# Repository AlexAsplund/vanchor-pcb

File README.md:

# Vanchor PCBs (helm v4.2 + thrust driver v1.1)

Carrier PCB for the [vanchor-ng](../vanchor-ng) trolling-motor autopilot:
an **Orange Pi Zero 3** (autopilot computer) + **Raspberry Pi Pico 2**
(real-time motor controller, I²C slave) on one **125×95 mm 2-layer board
(standard 1 oz)**. Thrust power lives on the companion **thrust-driver
board** cabled to J13 (any IBT-2/BTS7960-class driver also works); the
steering-servo bridge is on board. **12 V-only** (car battery, 14.4 V
charging) — the 5 V rail comes from an XL4015 buck module soldered on as a
daughterboard (U5). Full system diagrams: **`docs/architecture.md`**.

```mermaid
graph LR
    BATT[("12V battery")] -->|"J16, F1 10A, rev-FET"| VIN["VIN"]
    BATT ==>|"fat cable + ANL fuse"| TD["thrust driver board<br/>(J13 8-wire cable)"]
    VIN --> U5["U5 XL4015 buck 5V"] --> SBC["Orange Pi Zero 3 / RPi<br/>(J1 ribbon) + screen + fan"]
    VIN --> SRV["2x BTN8982TA servo bridge"] -->|"J22"| SM["12V worm servo"]
    SBC <-->|"I2C3"| PICO["Pico 2 @0x42"]
    PICO -->|"GP12-15 PWM"| TD --> M(("trolling motor"))
    PICO --> SRV
    SM -->|"AS5600, J11"| PICO
    SBC -.->|"WiFi"| TAB["tablet"]
    HWT["HWT901B AHRS"] -->|"J3 UART5"| SBC
    PICO <-->|"can2040 + J12 xcvr + J5"| N2K[("NMEA2000")]
```

*[static SVG](docs/diagrams/readme-overview.svg) — full diagram set: `docs/architecture.md`*

Cost history: v1/v2 carried an on-board 800 W H-bridge; ten documented
cost-optimization passes (see `docs/cost-optimization-log.md`) brought a
12 V build from ~$111 to **~$41 per assembled board** (~$35 parts + ~$6 PCB).
The v2 on-board-bridge design remains available at git tag/commit `bf91c4a`.

## NMEA2000 / CAN provision (helm board)

CAN lives on the Pico 2 (can2040 PIO CAN on GP18/GP19, 250 kbit/s for
NMEA2000). Plug a 3.3 V CAN transceiver module (Waveshare SN65HVD230) onto
J12 with four jumper wires: pin 1 = 3V3, pin 8 = GND, pin 6 = GP18 -> CTX,
pin 7 = GP19 -> CRX. The N2K drop cable's CAN_H/L land on the module's
screw terminal; its power/shield conductors land on J5 (V+ / GND / SHIELD).
R41 (0R, DNP): fit to power the backbone from the battery input - add an
inline 2-3 A fuse in the drop cable if you do. R42 (0R, DNP): bond shield
to GND only if the network isn't grounded elsewhere.

## Boards

- `boards/helm/` — the helm/carrier board (Orange Pi Zero 3 *or* Raspberry Pi + Pico 2, servo
  bridge, XL4015 buck daughterboard, PWM output header J13).
- `boards/thrust-driver/` — 12-24 V trolling-motor H-bridge (2-4× BTN8982TA),
  connects to helm J13 with a straight 8-wire cable. See its README for the
  base (~30 A) vs high-power (~50 A) variants and the solder-lane
  reinforcement technique.

## Repository layout

| Path | Content |
|---|---|
| `boards/helm/` | KiCad 10 project (schematic, board, custom symbols/footprints) |
| `boards/helm/sheets/*.py` | Net-spec sources — the schematic is **generated** from these |
| `boards/helm/scripts/` | Generators + gates (`build_sch.sh`, `build_board.py`, ERC/DRC helpers) |
| `boards/helm/fab/` | Gerbers, drill, BOM — upload these to PCBWay/JLCPCB |
| `boards/thrust-driver/` | Companion H-bridge board (own README, sheets, scripts, fab) |
| `docs/architecture.md` | **System diagrams**: WiFi/tablet, NMEA0183+2000, HWT901B, control loop |
| `docs/cost-optimization-log.md` | The 10 cost passes and their effect |
| `docs/superpowers/` | Design spec + implementation plan |
| `.claude/skills/` | kicad-happy review skills (vendored) |

## Regenerating the design

```sh
docker compose up -d                 # KiCad 10 container (GUI at https://localhost:3001)
./boards/helm/scripts/build_sch.sh      # specs -> .kicad_sch + ERC
docker exec vanchor-kicad kicad-cli sch export netlist --format kicadsexpr \
    -o /config/vanchor-pcb/boards/helm/vanchor-helm.net /config/vanchor-pcb/boards/helm/vanchor-helm.kicad_sch
docker exec -e BASE_GND=0 vanchor-kicad python3 /config/vanchor-pcb/boards/helm/scripts/build_board.py
# route with freerouting-1.9 (see git history for the exact docker command),
# then: docker exec vanchor-kicad python3 /config/vanchor-pcb/boards/helm/scripts/import_routes.py
```

## Connector map

| Ref | Label | Wire to |
|---|---|---|
| J16 | BATT 12V | battery + / − (board logic + servo supply; ≥1.5 mm²) |
| J13 | THRUST DRV | external driver, IBT-2 pin order: **1 RPWM · 2 LPWM · 3 R_EN · 4 L_EN · 5 R_IS · 6 L_IS · 7 VCC(5V) · 8 GND** |
| J22 | SERVO MOTOR | 12 V worm gearmotor of the steering servo |
| U5 | XL4015 BUCK | the module solders ON: pins into its 4 corner terminals, spacers, into the slotted pads (set 5.1 V first!) |
| J1 | OPI Z3 26-PIN | male header → 26-way 1:1 IDC ribbon (original-RPi style) to the Zero 3 |
| J11 | AS5600 | 4-wire cable into servo housing: 3V3 GND SDA SCL (≤1 m, twisted) |
| J3 | UART5 | **HWT901B AHRS** / GPS / NMEA0183-TTL (3V3 TTL, PH2/PH3; `uart5` overlay; wiring in `docs/architecture.md`) |
| J4 | UART2 | second serial device (PC5/PC6; enable `uart2` overlay; swap TX/RX at the JST if silent) |
| J8 | I2C3 spare | I²C sensors (bus shared with Pico link — keep short) |
| J10 | AUX 5V | fused 5 V for a screen or accessory |
| J9 | FAN + HALL | pin 1-2: 5 V fan; pin 3: **steering-zero hall switch** (A3144-class open-collector, magnet at servo center; 10 k pullup to 3V3 + RC on board, reads on Pico GP0) |
| J5 | NMEA2000 PWR | N2K drop-cable V+ / GND / SHIELD (CAN_H/L go to the transceiver module) |
| J2 | SBC2 | second SBC port: same 26-pin bus as J1, classic RPi positions — fit ONE SBC only (DNP) |
| J12 | PICO UTIL | spare Pico I/O; carries the CAN transceiver hookup (pins 1/8/6/7, see NMEA2000 section) |

Battery→motor power wiring (fat cables, ANL fuse) goes to the **thrust
driver board**, not to this board.

## Mechanical

- The Zero 3 (pre-soldered pins-up variant) connects via a **standard
  26-way 1:1 IDC ribbon** (~$1.50, original-Raspberry-Pi style) from its
  header to J1 — match pin 1 (marked) on both ends. The module mounts
  wherever suits the enclosure; the two spare M3 holes near J1 can carry a
  small mounting plate.
- The module is powered through the ribbon 5 V pins — do **not** also plug
  USB-C power. Keep the ribbon short (≤15 cm) — it carries I²C and the
  module's supply. The 3.3 V for the JST headers comes from the module's
  regulator (keep attached loads under ~200 mA total).
- J1 pins 14 & 20 and J2 pin 9 are deliberately NC (each connector keeps
  at least three other ground pins; the header escape routing owns those
  corridors).
- J2/J12 are DNP debug breakouts whose outlines slightly overlap — populate
  at most one, or use a right-angle header on J12.
- 4× M3 corner mounting holes. No heatsink needed on this board.

## Power & safety notes

- F1 (10 A mini blade) fuses everything on this board. The thrust path is
  fused externally at the battery per your driver's rating.
- **Thrust**: GP12-15 drive the external driver's RPWM/LPWM/R_EN/L_EN at
  3.3 V (fine for BTS7960-class VIH ≈ 2.5 V). 100k pull-downs on both EN pins
  keep the driver disabled when the Pico is absent/in reset. R_IS/L_IS are
  mixed (2× 1k), loaded (20k), filtered and BAT54S-clamped into Pico ADC1.
- **Servo bridge**: 2× BTN8982TA (built-in protection), fed battery-direct
  from protected VIN. Board plumbing is sized for ~5 A continuous /
  ~10 A peak servo current (F1, terminal blocks, track widths).
- Telemetry: thrust current via the driver's IS pins (ADC1), servo current
  (ADC0), battery voltage (ADC2).
- Reverse polarity: IRF9540N high-side FET; SMCJ18A TVS (12 V clamp);
  2× 470 µF/25 V bulk.
- The buck module (U5) mounts as a daughterboard: solder 4 pins into the
  XL4015's corner terminals, slide 5-8 mm spacers on, solder into the
  slotted pads (slots absorb vendor hole-grid variance; buy the common 54×23 mm module
  variant (nominal 49×18 mm hole grid) — the smaller 51×26 mm variant has a
  different grid that may not fit; verify against your module). Set 5.1 V and load-test at 4 A BEFORE
  soldering it in. R20/R21/D10/D11 sit under the module's edge — fit them
  first.
- Firmware contract: I²C slave 0x42, reg 0x00 CMD {pwm u8, dir u8, steer i8},
  reg 0x10 STATUS {angle f32, ok u8, wrap i8, state u8, vbat_mV u16,
  isense u16}; 800 ms watchdog → thrust 0, steering holds (worm self-locks).
  Pin deltas vs v2: thrust on **GP12=RPWM GP13=LPWM GP14=R_EN GP15=L_EN**;
  GP16/GP26 freed.
- Zero 3 side: I²C3 (`i2c3` overlay) for the Pico link, `uart2`/`uart5`
  overlays for the JSTs; Pico RUN on PC11, SWD reflash via PC15 (SWDIO) /
  PC14 (SWCLK) — openocd sysfsgpio/libgpiod driver on the H618.

## Bring-up checklist

1. Visual + continuity: VIN↔GND, 5V↔GND, 12V↔GND not shorted.
2. No Zero 3/Pico fitted. Feed 12 V into J16: VIN LED lights; verify the
   buck module outputs 5.0-5.2 V on J1 pins 2/4.
3. Fit the Pico only (no Zero 3): flash test firmware over USB, check I²C
   pull-ups, exercise LED_STAT.
4. Plug in the Zero 3 (pin 1 to the marked corner!). `i2cdetect -y 3` →
   device at 0x42.
5. Connect AS5600 cable: Pico reads angle; rotate servo shaft by hand.
6. Servo closed-loop test with the gearmotor on a bench supply.
7. Connect the external thrust driver to J13, small test motor on its
   outputs: verify PWM, direction, the EN failsafe (reset the Pico mid-run →
   driver must drop out) and IS telemetry on ADC1.
8. Only then wire the real trolling motor through the external driver.

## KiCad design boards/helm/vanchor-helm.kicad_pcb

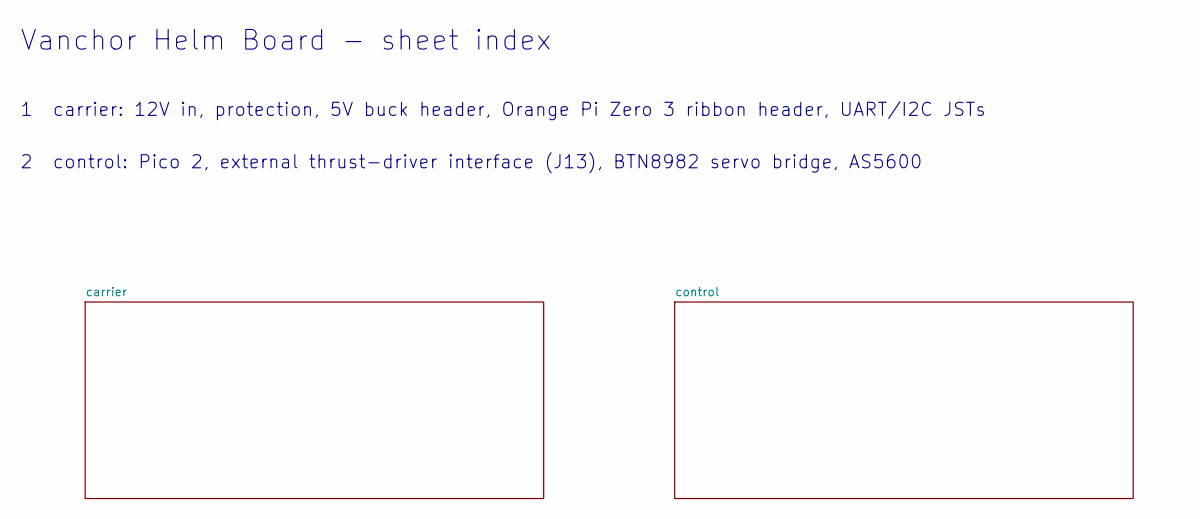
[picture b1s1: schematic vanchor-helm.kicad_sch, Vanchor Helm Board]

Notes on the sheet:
Vanchor Helm Board - sheet index
1 carrier: 12V in, protection, 5V buck header, Orange Pi Zero 3 ribbon header, UART/I2C JSTs
2 control: Pico 2, external thrust-driver interface (J13), BTN8982 servo bridge, AS5600

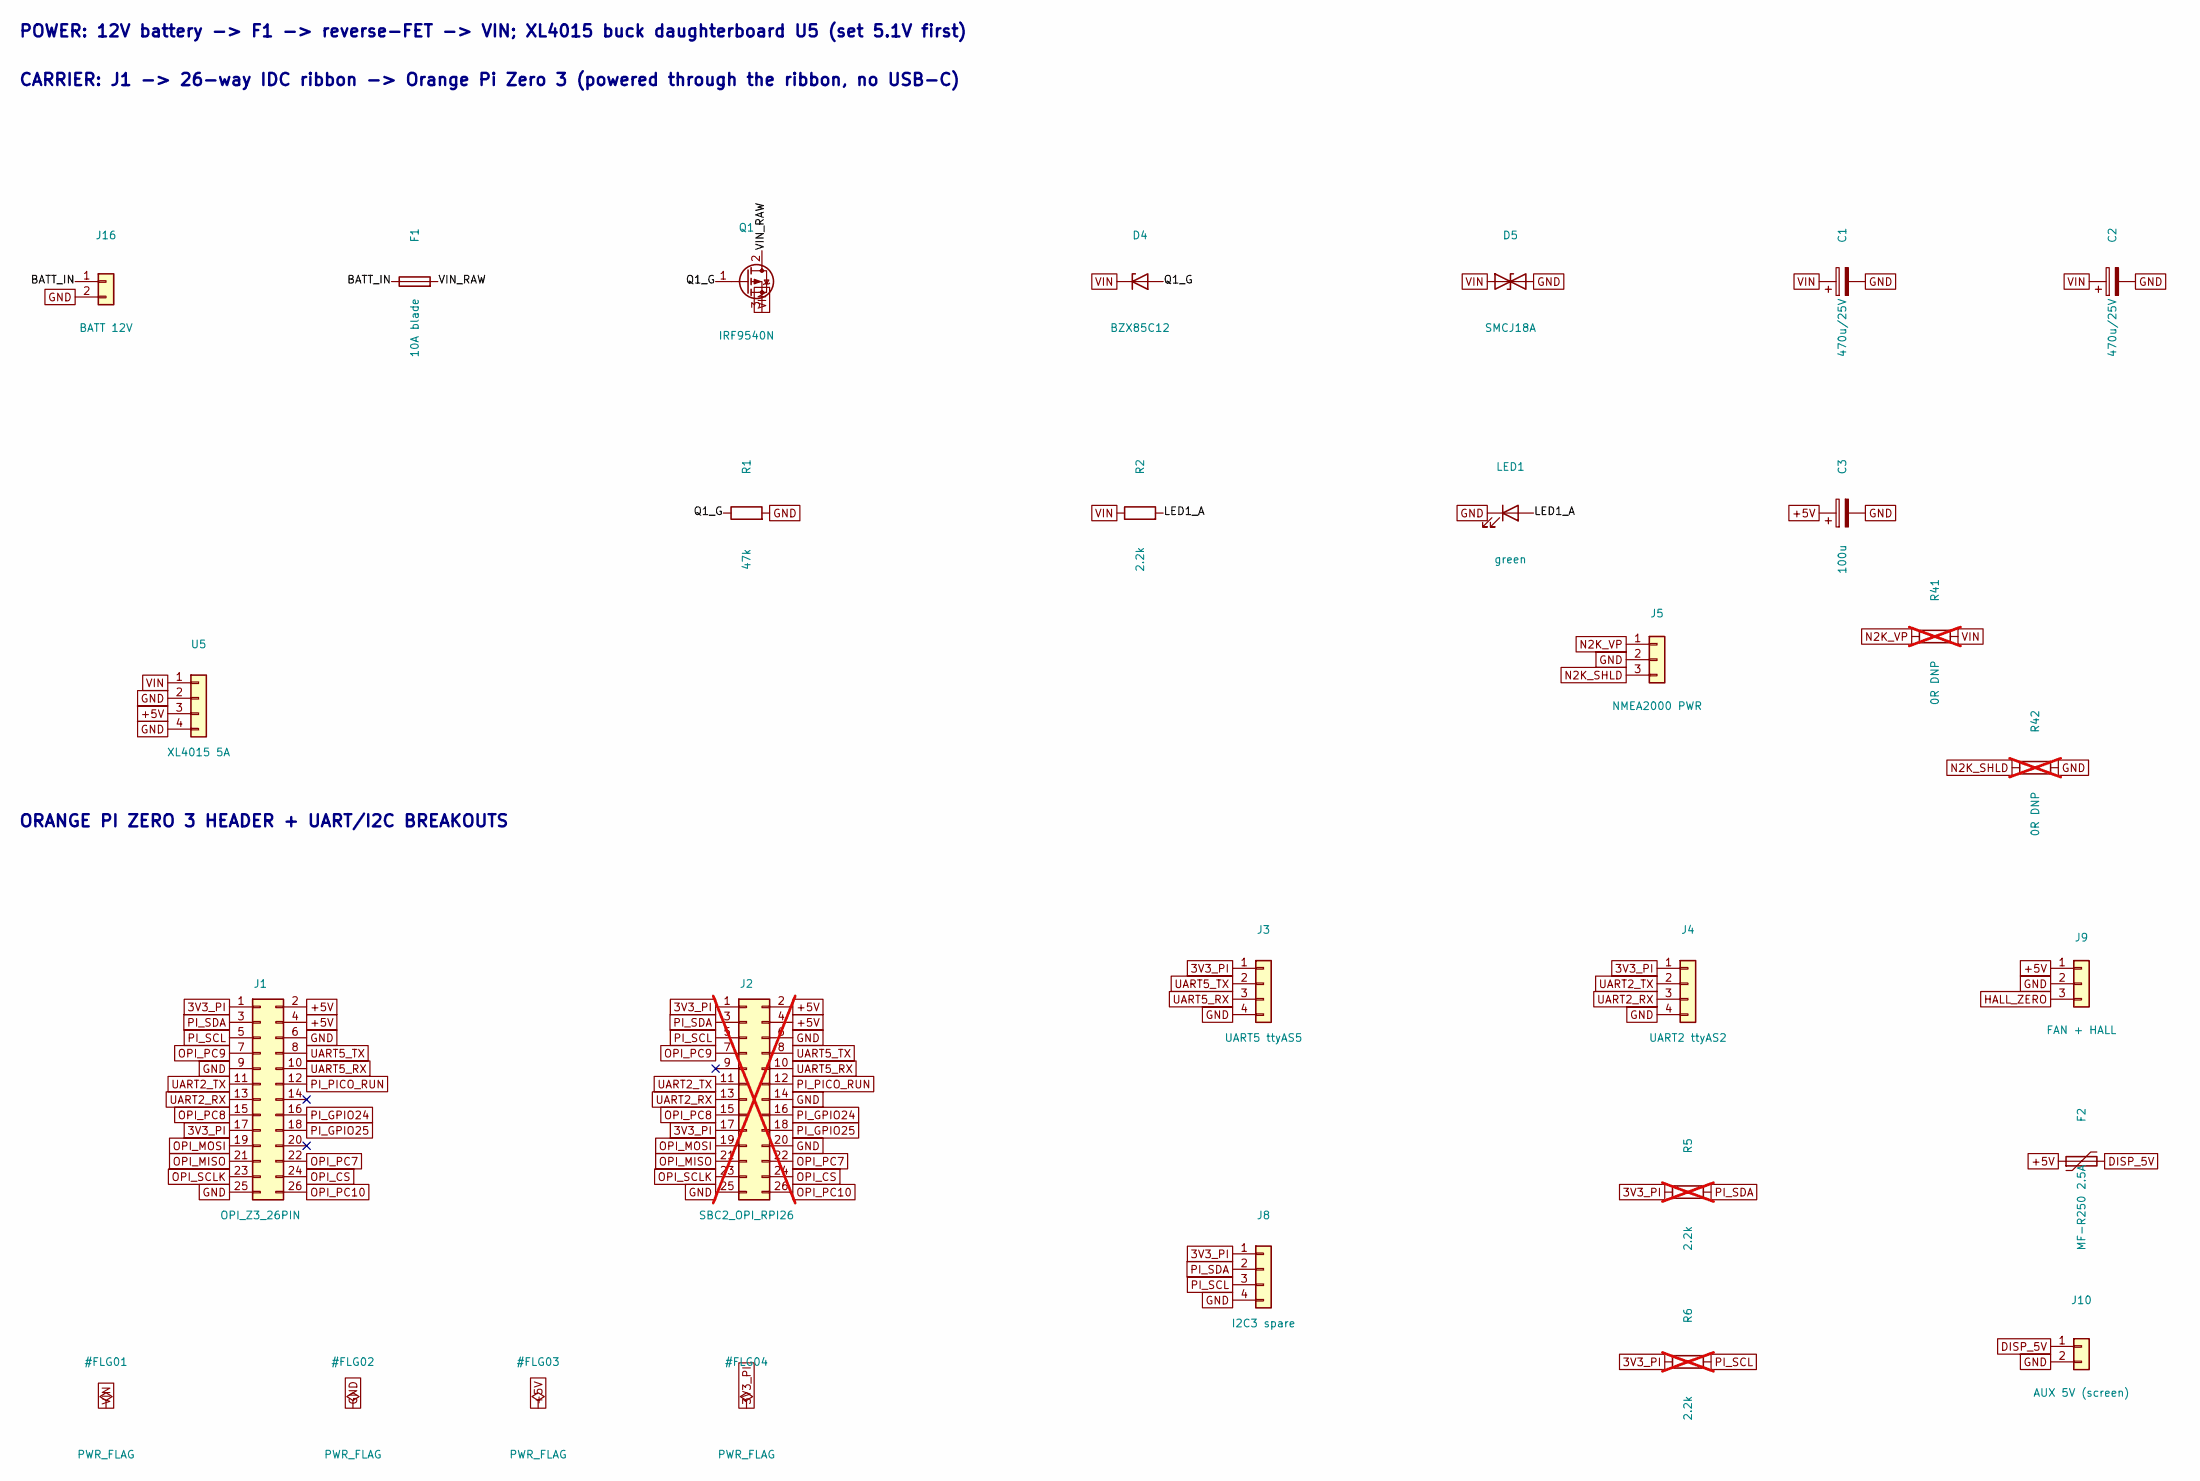
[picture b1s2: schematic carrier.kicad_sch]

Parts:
C1, C2: 470u/25V; CP_Radial_D12.5mm_P5.00mm; MPN EEU-FR1E471B
C3: 100u; CP_Radial_D6.3mm_P2.50mm; MPN EEU-FR1E101
D4: BZX85C12; D_DO-41_SOD81_P10.16mm_Horizontal; MPN BZX85C12-TAP
D5: SMCJ18A; D_SMC; MPN SMCJ18A
F1: 10A blade; Fuseholder_Blade_Mini_Keystone_3568; MPN 3568
F2: MF-R250 2.5A; MF-R250_Straight; MPN MF-R250
J1: OPI_Z3_26PIN; PinHeader_2x13_P2.54mm_Vertical; MPN 61302621121 (Wurth 2x13 2.54mm male hea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
J2: SBC2_OPI_RPI26; PinHeader_2x13_P2.54mm_Vertical; not fitted
J3: UART5 ttyAS5; JST_XH_B4B-XH-A_1x04_P2.50mm_Vertical; MPN JST B4B-XH-A(LF)(SN)
J4: UART2 ttyAS2; JST_XH_B4B-XH-A_1x04_P2.50mm_Vertical; MPN JST B4B-XH-A(LF)(SN)
J5: NMEA2000 PWR; JST_XH_B3B-XH-A_1x03_P2.50mm_Vertical; MPN JST B4B-XH-A(LF)(SN)
J8: I2C3 spare; JST_XH_B4B-XH-A_1x04_P2.50mm_Vertical; MPN JST B4B-XH-A(LF)(SN)
J9: FAN + HALL; PinHeader_1x03_P2.54mm_Vertical
J10: AUX 5V (screen); JST_XH_B2B-XH-A_1x02_P2.50mm_Vertical; MPN JST B2B-XH-A(LF)(SN)
J16: BATT 12V; TerminalBlock_CUI_TB007-508-02_1x02_P5.08mm_Horizontal
LED1: green; LED_D5.0mm
Q1: IRF9540N; TO-220-3_Vertical; MPN IRF9540NPBF
R1: 47k; R_Axial_DIN0207_L6.3mm_D2.5mm_P10.16mm_Horizontal
R2: 2.2k; R_Axial_DIN0207_L6.3mm_D2.5mm_P10.16mm_Horizontal
R5, R6: 2.2k; R_Axial_DIN0207_L6.3mm_D2.5mm_P10.16mm_Horizontal; not fitted
R41, R42: 0R DNP; R_Axial_DIN0207_L6.3mm_D2.5mm_P2.54mm_Vertical; not fitted
U5: XL4015 5A; XL4015_Module; MPN XL4015 5A module (AliExpress)

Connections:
3V3_PI: J1.1, J1.17, J2.1, J2.17, J3.1, J4.1, J8.1, R5.1, R6.1
+5V: C3.1, F2.1, J1.2, J1.4, J2.2, J2.4, J9.1, U5.3; also elsewhere on the board
/carrier/BATT_IN: F1.1, J16.1
/carrier/LED1_A: LED1.2 (A), R2.2
/carrier/Q1_G: D4.2 (A), Q1.1 (G), R1.1
/carrier/VIN_RAW: F1.2, Q1.2 (D)
DISP_5V: F2.2, J10.1
GND: C1.2, C2.2, C3.2, D5.2 (A2), J1.6, J1.9, J1.25, J2.6, J2.14, J2.20, J2.25, J3.4, J4.4, J5.2, J8.4, J9.2, J10.2, J16.2, LED1.1 (K), R1.2, R42.2, U5.2, U5.4; also elsewhere on the board
HALL_ZERO: J9.3; also elsewhere on the board
N2K_SHLD: J5.3, R42.1
N2K_VP: J5.1, R41.1
OPI_CS: J1.24, J2.24
OPI_MISO: J1.21, J2.21
OPI_MOSI: J1.19, J2.19
OPI_PC7: J1.22, J2.22
OPI_PC8: J1.15, J2.15
OPI_PC9: J1.7, J2.7
OPI_PC10: J1.26, J2.26
OPI_SCLK: J1.23, J2.23
PI_GPIO24: J1.16, J2.16; also elsewhere on the board
PI_GPIO25: J1.18, J2.18; also elsewhere on the board
PI_PICO_RUN: J1.12, J2.12; also elsewhere on the board
PI_SCL: J1.5, J2.5, J8.3, R6.2; also elsewhere on the board
PI_SDA: J1.3, J2.3, J8.2, R5.2; also elsewhere on the board
UART2_RX: J1.13, J2.13, J4.3
UART2_TX: J1.11, J2.11, J4.2
UART5_RX: J1.10, J2.10, J3.3
UART5_TX: J1.8, J2.8, J3.2
VIN: C1.1, C2.1, D4.1 (K), D5.1 (A1), Q1.3 (S), R2.1, R41.2, U5.1; also elsewhere on the board

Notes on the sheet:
POWER: 12V battery -> F1 -> reverse-FET -> VIN; XL4015 buck daughterboard U5 (set 5.1V first)
CARRIER: J1 -> 26-way IDC ribbon -> Orange Pi Zero 3 (powered through the ribbon, no USB-C)
ORANGE PI ZERO 3 HEADER + UART/I2C BREAKOUTS

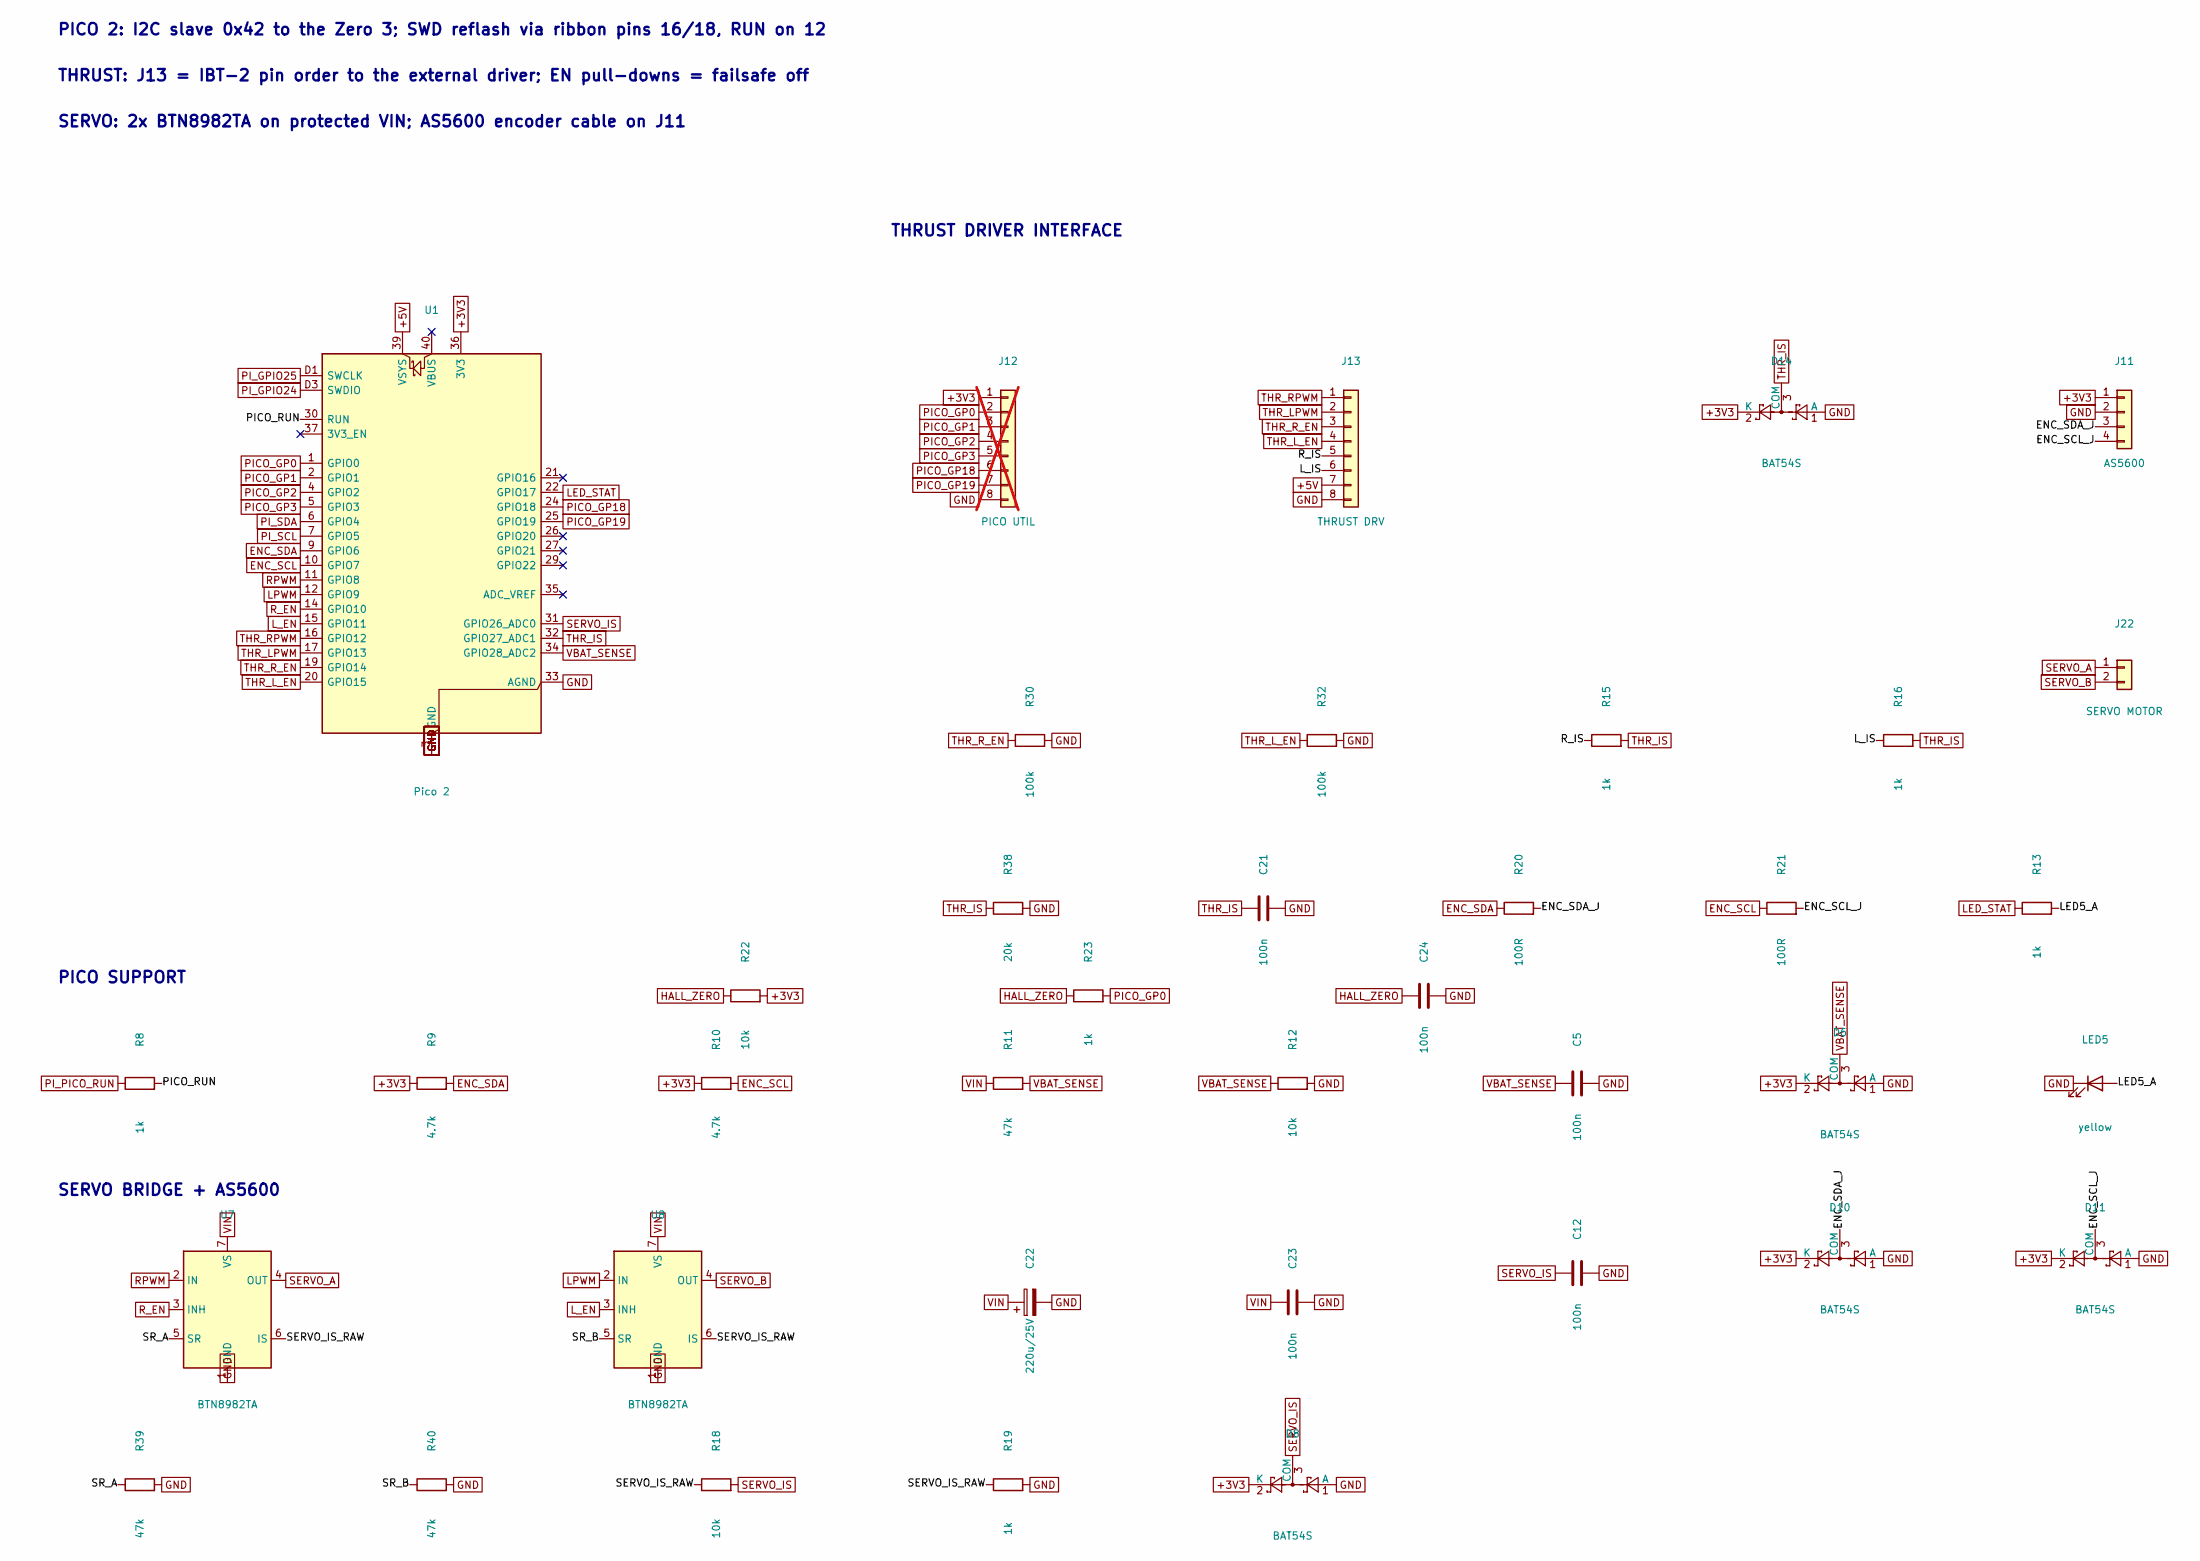
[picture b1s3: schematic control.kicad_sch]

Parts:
C5, C12, C21, C23: 100n; C_Disc_D5.0mm_W2.5mm_P5.00mm
C22: 220u/25V; CP_Radial_D8.0mm_P3.50mm; MPN EEU-FR1E221 (220uF/25V)
C24: 100n; C_0805_2012Metric
D6, D8, D10, D11, D14: BAT54S; SOT-23; MPN BAT54S,215
J11: AS5600; JST_XH_B4B-XH-A_1x04_P2.50mm_Vertical; MPN JST B4B-XH-A(LF)(SN)
J12: PICO UTIL; PinHeader_1x08_P2.54mm_Vertical; not fitted
J13: THRUST DRV; PinHeader_1x08_P2.54mm_Vertical
J22: SERVO MOTOR; TerminalBlock_CUI_TB007-508-02_1x02_P5.08mm_Horizontal; MPN CUI TB007-508-02
LED5: yellow; LED_D5.0mm
R8, R13, R15, R16, R19: 1k; R_Axial_DIN0207_L6.3mm_D2.5mm_P10.16mm_Horizontal
R9, R10: 4.7k; R_Axial_DIN0207_L6.3mm_D2.5mm_P10.16mm_Horizontal
R11, R39, R40: 47k; R_Axial_DIN0207_L6.3mm_D2.5mm_P10.16mm_Horizontal
R12, R18: 10k; R_Axial_DIN0207_L6.3mm_D2.5mm_P10.16mm_Horizontal
R20, R21: 100R; R_Axial_DIN0207_L6.3mm_D2.5mm_P10.16mm_Horizontal
R22: 10k; R_0805_2012Metric
R23: 1k; R_0805_2012Metric
R30, R32: 100k; R_Axial_DIN0207_L6.3mm_D2.5mm_P10.16mm_Horizontal
R38: 20k; R_Axial_DIN0207_L6.3mm_D2.5mm_P10.16mm_Horizontal
U1: Pico 2; RaspberryPi_Pico_TH_SWD; MPN Raspberry Pi Pico 2 (SC1632)
U7, U8: BTN8982TA; TO-263-7_TabPin4; MPN BTN8982TA

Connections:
+3V3: D6.2 (K), D8.2 (K), D10.2 (K), D11.2 (K), D14.2 (K), J11.1, J12.1, R9.1, R10.1, R22.2, U1.36 (3V3)
+5V: J13.7, U1.39 (VSYS); also elsewhere on the board
/control/ENC_SCL_J: D11.3 (COM), J11.4, R21.2
/control/ENC_SDA_J: D10.3 (COM), J11.3, R20.2
/control/LED5_A: LED5.2 (A), R13.2
/control/L_IS: J13.6, R16.1
/control/PICO_RUN: R8.2, U1.30 (RUN)
/control/R_IS: J13.5, R15.1
/control/SERVO_IS_RAW: R18.1, R19.1, U7.6 (IS), U8.6 (IS)
/control/SR_A: R39.1, U7.5 (SR)
/control/SR_B: R40.1, U8.5 (SR)
ENC_SCL: R10.2, R21.1, U1.10 (GPIO7)
ENC_SDA: R9.2, R20.1, U1.9 (GPIO6)
GND: C5.2, C12.2, C21.2, C22.2, C23.2, C24.2, D6.1 (A), D8.1 (A), D10.1 (A), D11.1 (A), D14.1 (A), J11.2, J12.8, J13.8, LED5.1 (K), R12.2, R19.2, R30.2, R32.2, R38.2, R39.2, R40.2, U1.3 (GND), U1.8 (GND), U1.13 (GND), U1.18 (GND), U1.23 (GND), U1.28 (GND), U1.33 (AGND), U1.38 (GND), U1.D2 (GND), U7.1 (GND), U8.1 (GND); also elsewhere on the board
HALL_ZERO: C24.1, R22.1, R23.1; also elsewhere on the board
LED_STAT: R13.1, U1.22 (GPIO17)
LPWM: U1.12 (GPIO9), U8.2 (IN)
L_EN: U1.15 (GPIO11), U8.3 (INH)
PICO_GP0: J12.2, R23.2, U1.1 (GPIO0)
PICO_GP1: J12.3, U1.2 (GPIO1)
PICO_GP2: J12.4, U1.4 (GPIO2)
PICO_GP3: J12.5, U1.5 (GPIO3)
PICO_GP18: J12.6, U1.24 (GPIO18)
PICO_GP19: J12.7, U1.25 (GPIO19)
PI_GPIO24: U1.D3 (SWDIO); also elsewhere on the board
PI_GPIO25: U1.D1 (SWCLK); also elsewhere on the board
PI_PICO_RUN: R8.1; also elsewhere on the board
PI_SCL: U1.7 (GPIO5); also elsewhere on the board
PI_SDA: U1.6 (GPIO4); also elsewhere on the board
RPWM: U1.11 (GPIO8), U7.2 (IN)
R_EN: U1.14 (GPIO10), U7.3 (INH)
SERVO_A: J22.1, U7.4 (OUT)
SERVO_B: J22.2, U8.4 (OUT)
SERVO_IS: C12.1, D8.3 (COM), R18.2, U1.31 (GPIO26_ADC0)
THR_IS: C21.1, D14.3 (COM), R15.2, R16.2, R38.1, U1.32 (GPIO27_ADC1)
THR_LPWM: J13.2, U1.17 (GPIO13)
THR_L_EN: J13.4, R32.1, U1.20 (GPIO15)
THR_RPWM: J13.1, U1.16 (GPIO12)
THR_R_EN: J13.3, R30.1, U1.19 (GPIO14)
VBAT_SENSE: C5.1, D6.3 (COM), R11.2, R12.1, U1.34 (GPIO28_ADC2)
VIN: C22.1, C23.1, R11.1, U7.7 (VS), U8.7 (VS); also elsewhere on the board

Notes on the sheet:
PICO 2: I2C slave 0x42 to the Zero 3; SWD reflash via ribbon pins 16/18, RUN on 12
THRUST: J13 = IBT-2 pin order to the external driver; EN pull-downs = failsafe off
SERVO: 2x BTN8982TA on protected VIN; AS5600 encoder cable on J11
THRUST DRIVER INTERFACE
PICO SUPPORT
SERVO BRIDGE + AS5600

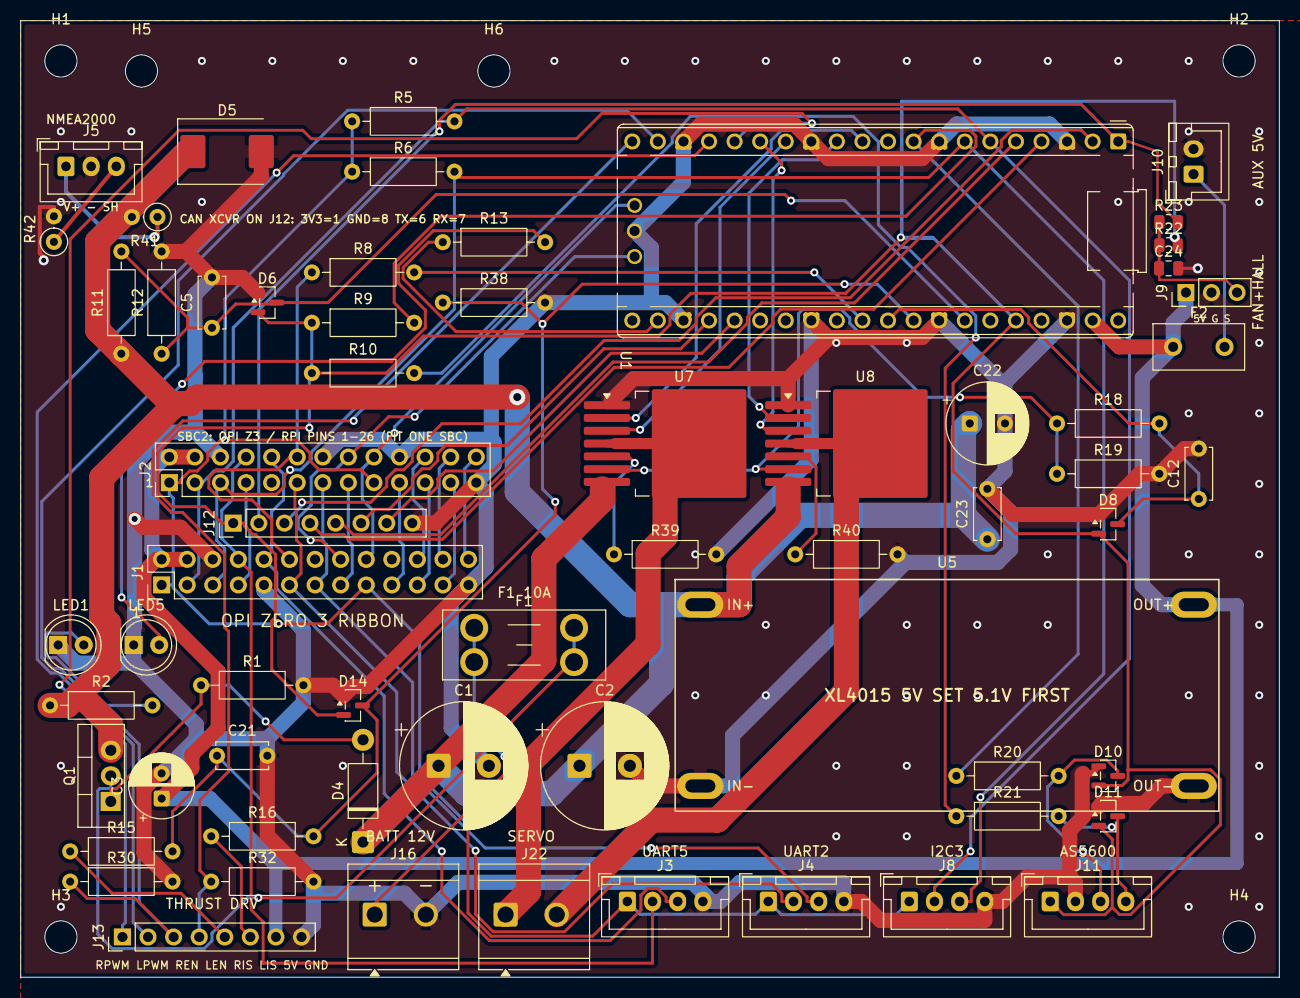
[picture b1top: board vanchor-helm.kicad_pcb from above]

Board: 2 copper layers, 125.0 x 95.0 mm, 69 parts (0 on the bottom side), 61 nets.

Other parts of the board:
H1, H2, H3, H4, H5, H6: MountingHole_3.2mm_M3

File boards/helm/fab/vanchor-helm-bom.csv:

"Ref","Value","Footprint","MPN","Qty","DNP"
"C1,C2","470u/25V","Capacitor_THT:CP_Radial_D12.5mm_P5.00mm","EEU-FR1E471B","2",""
"C3","100u","Capacitor_THT:CP_Radial_D6.3mm_P2.50mm","EEU-FR1E101","1",""
"C5,C12,C21,C23","100n","Capacitor_THT:C_Disc_D5.0mm_W2.5mm_P5.00mm","","4",""
"C22","220u/25V","Capacitor_THT:CP_Radial_D8.0mm_P3.50mm","EEU-FR1E221 (220uF/25V)","1",""
"C24","100n","Capacitor_SMD:C_0805_2012Metric","","1",""
"D4","BZX85C12","Diode_THT:D_DO-41_SOD81_P10.16mm_Horizontal","BZX85C12-TAP","1",""
"D5","SMCJ18A","Diode_SMD:D_SMC","SMCJ18A","1",""
"D6,D8,D10,D11,D14","BAT54S","Package_TO_SOT_SMD:SOT-23","BAT54S,215","5",""
"F1","10A blade","Fuse:Fuseholder_Blade_Mini_Keystone_3568","3568","1",""
"F2","MF-R250 2.5A","vanchor-helm:MF-R250_Straight","MF-R250","1",""
"J1","OPI_Z3_26PIN","Connector_PinHeader_2.54mm:PinHeader_2x13_P2.54mm_Vertical","61302621121 (Wurth 2x13 2.54mm male header)","1",""
"J2","SBC2_OPI_RPI26","Connector_PinHeader_2.54mm:PinHeader_2x13_P2.54mm_Vertical","","1","DNP"
"J3","UART5 ttyAS5","Connector_JST:JST_XH_B4B-XH-A_1x04_P2.50mm_Vertical","JST B4B-XH-A(LF)(SN)","1",""
"J4","UART2 ttyAS2","Connector_JST:JST_XH_B4B-XH-A_1x04_P2.50mm_Vertical","JST B4B-XH-A(LF)(SN)","1",""
"J5","NMEA2000 PWR","Connector_JST:JST_XH_B3B-XH-A_1x03_P2.50mm_Vertical","JST B4B-XH-A(LF)(SN)","1",""
"J8","I2C3 spare","Connector_JST:JST_XH_B4B-XH-A_1x04_P2.50mm_Vertical","JST B4B-XH-A(LF)(SN)","1",""
"J9","FAN + HALL","Connector_PinHeader_2.54mm:PinHeader_1x03_P2.54mm_Vertical","","1",""
"J10","AUX 5V (screen)","Connector_JST:JST_XH_B2B-XH-A_1x02_P2.50mm_Vertical","JST B2B-XH-A(LF)(SN)","1",""
"J11","AS5600","Connector_JST:JST_XH_B4B-XH-A_1x04_P2.50mm_Vertical","JST B4B-XH-A(LF)(SN)","1",""
"J12","PICO UTIL","Connector_PinHeader_2.54mm:PinHeader_1x08_P2.54mm_Vertical","","1","DNP"
"J13","THRUST DRV","Connector_PinHeader_2.54mm:PinHeader_1x08_P2.54mm_Vertical","","1",""
"J16","BATT 12V","TerminalBlock_CUI:TerminalBlock_CUI_TB007-508-02_1x02_P5.08mm_Horizontal","","1",""
"J22","SERVO MOTOR","TerminalBlock_CUI:TerminalBlock_CUI_TB007-508-02_1x02_P5.08mm_Horizontal","CUI TB007-508-02","1",""
"LED1","green","LED_THT:LED_D5.0mm","","1",""
"LED5","yellow","LED_THT:LED_D5.0mm","","1",""
"Q1","IRF9540N","Package_TO_SOT_THT:TO-220-3_Vertical","IRF9540NPBF","1",""
"R1,R11,R39,R40","47k","Resistor_THT:R_Axial_DIN0207_L6.3mm_D2.5mm_P10.16mm_Horizontal","","4",""
"R2,R5,R6","2.2k","Resistor_THT:R_Axial_DIN0207_L6.3mm_D2.5mm_P10.16mm_Horizontal","","3","DNP"
"R8,R13,R15,R16,R19","1k","Resistor_THT:R_Axial_DIN0207_L6.3mm_D2.5mm_P10.16mm_Horizontal","","5",""
"R9,R10","4.7k","Resistor_THT:R_Axial_DIN0207_L6.3mm_D2.5mm_P10.16mm_Horizontal","","2",""
"R12,R18","10k","Resistor_THT:R_Axial_DIN0207_L6.3mm_D2.5mm_P10.16mm_Horizontal","","2",""
"R20,R21","100R","Resistor_THT:R_Axial_DIN0207_L6.3mm_D2.5mm_P10.16mm_Horizontal","","2",""
"R22","10k","Resistor_SMD:R_0805_2012Metric","","1",""
"R23","1k","Resistor_SMD:R_0805_2012Metric","","1",""
"R30,R32","100k","Resistor_THT:R_Axial_DIN0207_L6.3mm_D2.5mm_P10.16mm_Horizontal","","2",""
"R38","20k","Resistor_THT:R_Axial_DIN0207_L6.3mm_D2.5mm_P10.16mm_Horizontal","","1",""
"R41,R42","0R DNP","Resistor_THT:R_Axial_DIN0207_L6.3mm_D2.5mm_P2.54mm_Vertical","","2","DNP"
"U1","Pico 2","vanchor-helm:RaspberryPi_Pico_TH_SWD","Raspberry Pi Pico 2 (SC1632)","1",""
"U5","XL4015 5A","vanchor-helm:XL4015_Module","XL4015 5A module (AliExpress)","1",""
"U7,U8","BTN8982TA","Package_TO_SOT_SMD:TO-263-7_TabPin4","BTN8982TA","2",""
